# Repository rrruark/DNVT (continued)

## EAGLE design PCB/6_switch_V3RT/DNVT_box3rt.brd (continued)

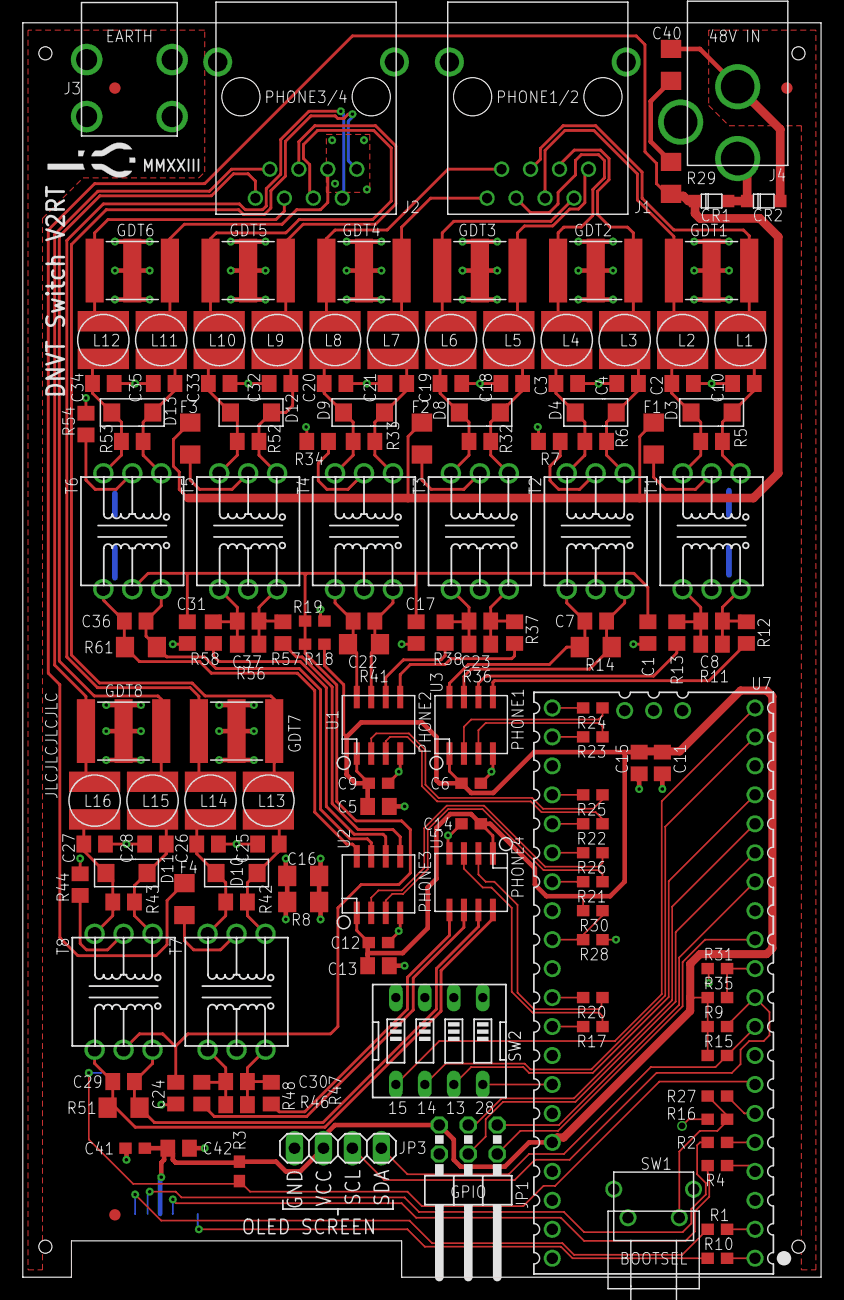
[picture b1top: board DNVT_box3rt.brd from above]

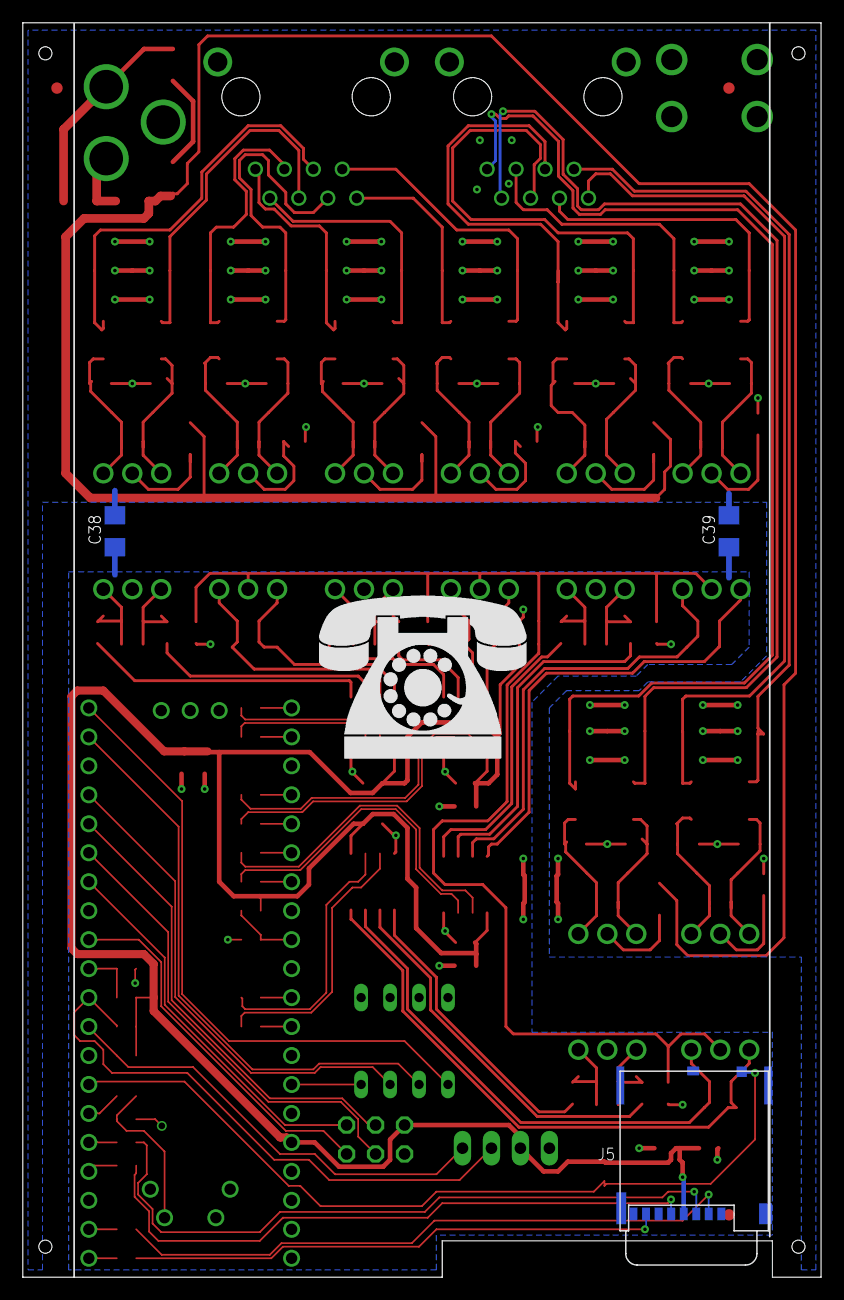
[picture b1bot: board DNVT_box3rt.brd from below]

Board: 2 copper layers, 70.0 x 110.0 mm, 155 parts (3 on the bottom side), 111 nets.

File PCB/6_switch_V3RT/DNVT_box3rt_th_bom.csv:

Qty;Value;Device;Package;Parts;Description;Assembled by JLCPCB;PARTNO;LCSC;SPICEPREFIX;VALUE
1;;PINHD-1X4;1X04;JP3;PIN HEADER;No;2057-PH1-04-UA-ND;C2691448;;
1;;PINHD-2X3/90;2X03/90;JP1;PIN HEADER;No;2057-PH2RA-06-UA-ND;C2935935;;
1;;SW_DIP-4;EDG-04;SW2;DIP SWITCH;No;2449-KG04E-ND;C962226;;
4;0;R-US_R0805;R0805;R7, R34, R44, R54;RESISTOR, American symbol;Yes;;;R;
5;0.1uF;0603_CAPACITOR;603;C6, C9, C12, C14, C41;0603 Capacitor -- WARNING: NO DEFINED VALUE OR PART NUMBER;Yes;;;;sel
15;10;0603_RESISTOR;603;R1, R2, R4, R10, R17, R20, R21, R22, R23, R24, R25, R26, R27, R28, R31;0603 Resistor -- WARNING: NO DEFINED PART NUMBER OR VALUE;Yes;;;;sel
1;10;1206_RESISTOR;1206;R29;NO DEFINED PN;Yes;;;;sel
3;10k;0603_RESISTOR;603;R3, R9, R15;0603 Resistor -- WARNING: NO DEFINED PART NUMBER OR VALUE;Yes;;;;sel
4;120;1206_RESISTOR;1206;R14, R41, R51, R61;NO DEFINED PN;Yes;;;;sel
4;1206_FUSE;1206_FUSE;1206;F1, F2, F3, F4;;Yes;;;;
1;1M;1206_RESISTOR;1206;R8;NO DEFINED PN;Yes;;;;sel
2;1k;0603_RESISTOR;603;R18, R19;0603 Resistor -- WARNING: NO DEFINED PART NUMBER OR VALUE;Yes;;;;sel
24;1nF;0805_CAPACITOR;805;C2, C3, C4, C7, C8, C10, C18, C19, C20, C21, C22, C23, C25, C26, C27, C28, C29, C30, C32, C33, C34, C35, C36, C37;NO DEFINED PN;Yes;;;;
1;1nF;1206_CAPACITOR;1206;C16;NO DEFINED PN;Yes;;;;sel
9;1uF;0805_CAPACITOR;805;C1, C5, C11, C13, C15, C17, C24, C31, C42;NO DEFINED PN;Yes;;;;
1;1uF;1206_CAPACITOR;1206;C40;NO DEFINED PN;Yes;;;;sel
16;33uH;SDR0403-330KL;SDR0403;L1, L2, L3, L4, L5, L6, L7, L8, L9, L10, L11, L12, L13, L14, L15, L16;33 µH Unshielded Drum Core, Wirewound Inductor 640 mA 540mOhm Max Nonstandard;Yes;SDR0403-330KLCT-ND;;;33uH
8;470;R-US_R0805;R0805;R5, R11, R32, R36, R42, R46, R52, R56;RESISTOR, American symbol;Yes;;;R;
8;49.9;R-US_R0805;R0805;R12, R13, R37, R38, R47, R48, R57, R58;RESISTOR, American symbol;Yes;;;R;
8;600V;2036-60-SM-RPLF;2036_GDT;GDT1, GDT2, GDT3, GDT4, GDT5, GDT6, GDT7, GDT8;Gas Discharge Tube 600 V 10000A (10kA) ±20% 3 Pole Surface Mount;Yes;2036-60-SM-RPLFCT-ND;;;600V
8;78615/9C;78615/9C;786T;T1, T2, T3, T4, T5, T6, T7, T8;10mH General Purpose Pulse Transformer 1CT:1CT Surface Mount 56Vus;No;811-1261-5-ND;;;
1;8190;8190;7781;J3;4 Pin Screw Terminal, Power Tap 6-32 Through Hole, Right Angle;No;36-8190-ND;;;
2;A-2004-2-4-LPS-N-R;A-2004-2-4-LPS-N-R;A-2004-2-4-LPS-N-R;J1, J2;Jack Modular Connector 8p8c (RJ45, Ethernet) 90° Angle (Right) Shielded;No;AE10387-ND;;;
3;DNP;0603_RESISTOR;603;R16, R30, R35;0603 Resistor -- WARNING: NO DEFINED PART NUMBER OR VALUE;No;;;;sel
2;DNP;1206_CAPACITOR;1206;C38, C39;NO DEFINED PN;No;;;;sel
4;DNP;R-US_R0805;R0805;R6, R33, R43, R53;RESISTOR, American symbol;No;;;R;
2;ES1JFL;ES1JFL;SOD123(AK);CR1, CR2;Diode Standard 600 V 1A Surface Mount SOD-123F;Yes;ES1JFLCT-ND;;;
1;EVQ-PF008K;EVQ-PF008K;EVQ-PF008K;SW1;Tactile Switch SPST-NO Side Actuated Through Hole, Right Angle;No;P10880S-ND;;;
1;G-1005B;G-1005B;G-1005B;J4;"Power Barrel Connector Jack 2.50mm ID (0.098""), 5.50mm OD (0.217"") Through Hole, Right Angle";No;1939-G-1005B-ND;;;
4;ISL83490IBZ-T;ISL83490IBZ-T;SOIC8;U1, U2, U3, U5;1/1 Transceiver Full RS422, RS485 8-SOIC 3.3V;Yes;ISL83490IBZ-TCT-ND;;;
1;MEM2080-00-128-00-A;MEM2080-00-128-00-A;MEM2080;J5;9 (8 + 1) Position Card Connector Secure Digital - microSD™ Surface Mount, Right Angle Gold;No;2073-MEM2080-00-128-00-ACT-ND;;;
1;RASPBERRY_PICOTH;RASPBERRY_PICOTH;PICO-PKG-TH;U7;Raspberry Pi Pico;No;2648-SC0917-ND;;;
8;SMAJ5.0CA/TR7;SMAJ5.0CA/TR7;DO-214AC_NO_POL;D3, D4, D8, D9, D10, D11, D12, D13;9.2V Clamp 43.5A Ipp Tvs Diode Surface Mount DO-214AC (SMA);Yes;;;;
